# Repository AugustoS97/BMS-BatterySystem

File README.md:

# BMS-BatterySystem
Repositorio con el diseño de un BMS y una batería como Trabajo de Fin de Máster.
- Autor: Augusto Samuel Hernández Martín
- Tutor: Fernando Luis Rosa González
- Co-Tutor: Iván Rodríguez Méndez
- Titulación: Máster en Ingeniería Industrial
- Universidad de La Laguna, 2021

# Licencia
- El paquete: [GPLv3](LICENSE) © 2021 Augusto Samuel Hernández Martín - Universidad de La Laguna

# Resumen 
El presente Trabajo Fin de Máster consiste en el diseñado y fabricación de un Sistema de Gestión de Batería (BMS), así como una batería modular configurable a diferentes tensiones y capacidades, con el objetivo de poder alimentar sistemas electrónicos aislados como los dispositivos de capturas de índices de significación eco-acústicos. Se ha llevado a cabo el diseño electrónico de los diferentes módulos que forman el sistema de alimentación y gestión así como el cálculo y diseño de la batería a partir de celdas de ion-litio y su estructura mecánica. Para poder alimentar dicho sistema se ha dimensionado una posible instalación generadora, empleando energía fotovoltaica. Finalmente, se ha realizado la fabricación de los distintos elementos, tanto mecánicos como electrónicos, y el desarrollo software de las diferentes herramientas necesarias para la configuración del BMS, la captura y el análisis de los datos generados. Por último, se han propuesto y analizado diferentes aplicaciones, además de la mencionada como objetivo principal del proyecto, para este sistema de BMS y acumulador.

# Abstract

In the present Master’s Degree Final Project, a Battery Management System (BMS) has been designed and manufactured, as well as a modular battery configurable at different voltages and capacities, with the aim of being able to power isolated electronic systems such as devices for capturing eco-acoustic significance indexes. The electronic design of the different modules that make up the power supply and management system has been carried out, as well as the calculation and design of the battery based on lithium-ion cells and its mechanical structure. In order to be able to supply this system, a possible generating installation has been dimensioned, using photovoltaic energy. Finally, the manufacture of the different elements, both mechanical and electronic, and the software development of the different tools necessary for the configuration of the BMS and the capture and analysis of the data generated have been carried out. Finally, different applications have been proposed and analysed, in addition to the one mentioned as the main objective of the project, for this BMS and accumulator system.

# Imágenes del sistema desarrollado

# Sistema diseñado

El diagrama de bloques del sistema de alimentación y la batería es el siguiente:

La batería diseñada es la siguiente:

Los módulos electrónicos diseñados son los siguientes:

## BMS

## CAN2Serial

## CAN2RS485

# Contenido del repositorio

## Software
- BMS CAN Programmer: Puede encontrarse la herramienta BMS_CAN_Programer_GUI que debe ejecutarse en Linux con Qt 5 instalado. Y el firmware preparado para grabar en un ATMega 328P empleando la herramienta PlatformIo que realiza la conversión de los mensajes CAN del BMS desarrollado a mensajes serial que son leídos por la herramienta BMS_CAN_Programmer_GUI.
- SOC_estimation: Contiene los ficheros .csv de diferentes ensayos realizados a las celdas INR21700 de Samsung y en el directorio /src el script a ejecutar por terminal para obtener las curvas del ensayo. La carpeta /figures contiene las gráficas generadas.
- SmartBMS: Contiene el firmware del microcontrolador ATMega 328P del módulo de BMS. Debe flashearse empleando Platformio.
- bms_data_processing: Herramienta para ejecutar desde terminal e indicar la ruta del fichero .csv de datos del BMS generado así como número de celdas en serie y número de termistores.
-  power-monitor: Herramienta para instalar en una Raspberry Pi 3B+ que monitoriza el consumo de la misma a partir de las lecturas del integrado INA219 vía I2C. Almacena los ficheros capturados en un .json dentro del directorio /usr/share/power/data. Se generta un serivicio del sistema que puede ser gestionado mediante systemd.
-  power-data-processing: Herramienta que genera los gráficos de los datos capturados por power-monitor. Accede directamente a la ruta /home/$USER/power-data/data. Los diferentes ficheros python deben ubicarse en /home/$USER/power-data/src.

## Diseno-Electronico
- SmartBMS: Módulo electrónico de un BMS pra la medición de hasta 12 paquetes de celdas en serie, con comunicación CAN y medición de hasta 32 termistores NTC de 10KOhm. Opera con tensiones de alimentación de hasta 75V.
- CAN2Serial: Módulo electrónico para la interfaz de conversión de CAN a Serial para emplear la herramienta BMS_Programer_GUI y configurar el BMS.
- EPSolar-CAN: Módulo electrónico para la conversión de los mensajes CAN del BMS a mensajes para un cargador solar EPEver (mediante RS485).

## Diseno-Mecanico
- Bateria_horizontal.FCStd: Fichero FreeCAD con el diseño de un sistema de batería modular de 14.4V y 84Ah.
- Carcasa_Can2Serial.FCStd: Fichero FreeCAD con el diseno e la carcasa para la placa de circuito impreso de CAN2Serial
- STL: Contiene los modelos 3D de las diferentes piezas.

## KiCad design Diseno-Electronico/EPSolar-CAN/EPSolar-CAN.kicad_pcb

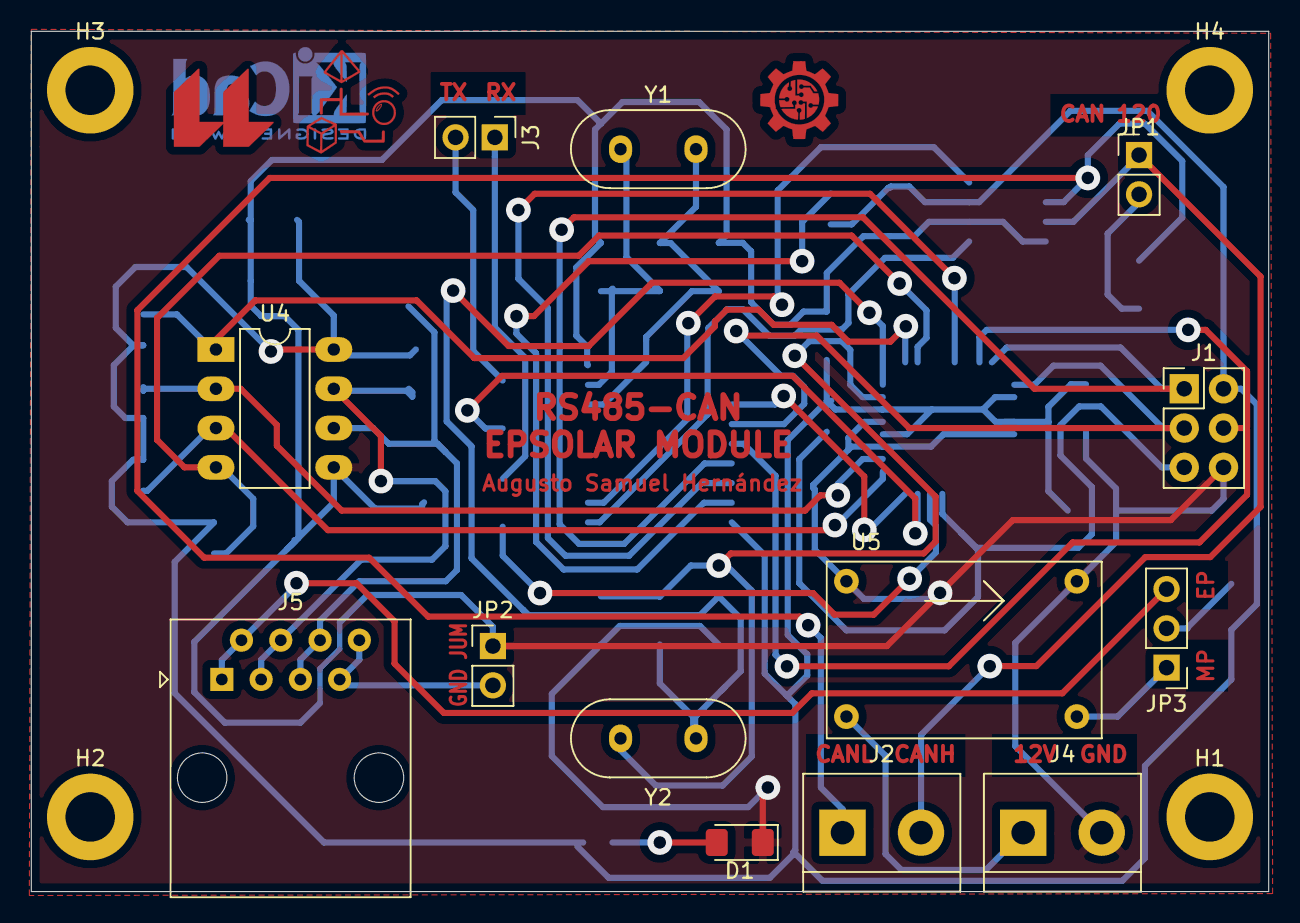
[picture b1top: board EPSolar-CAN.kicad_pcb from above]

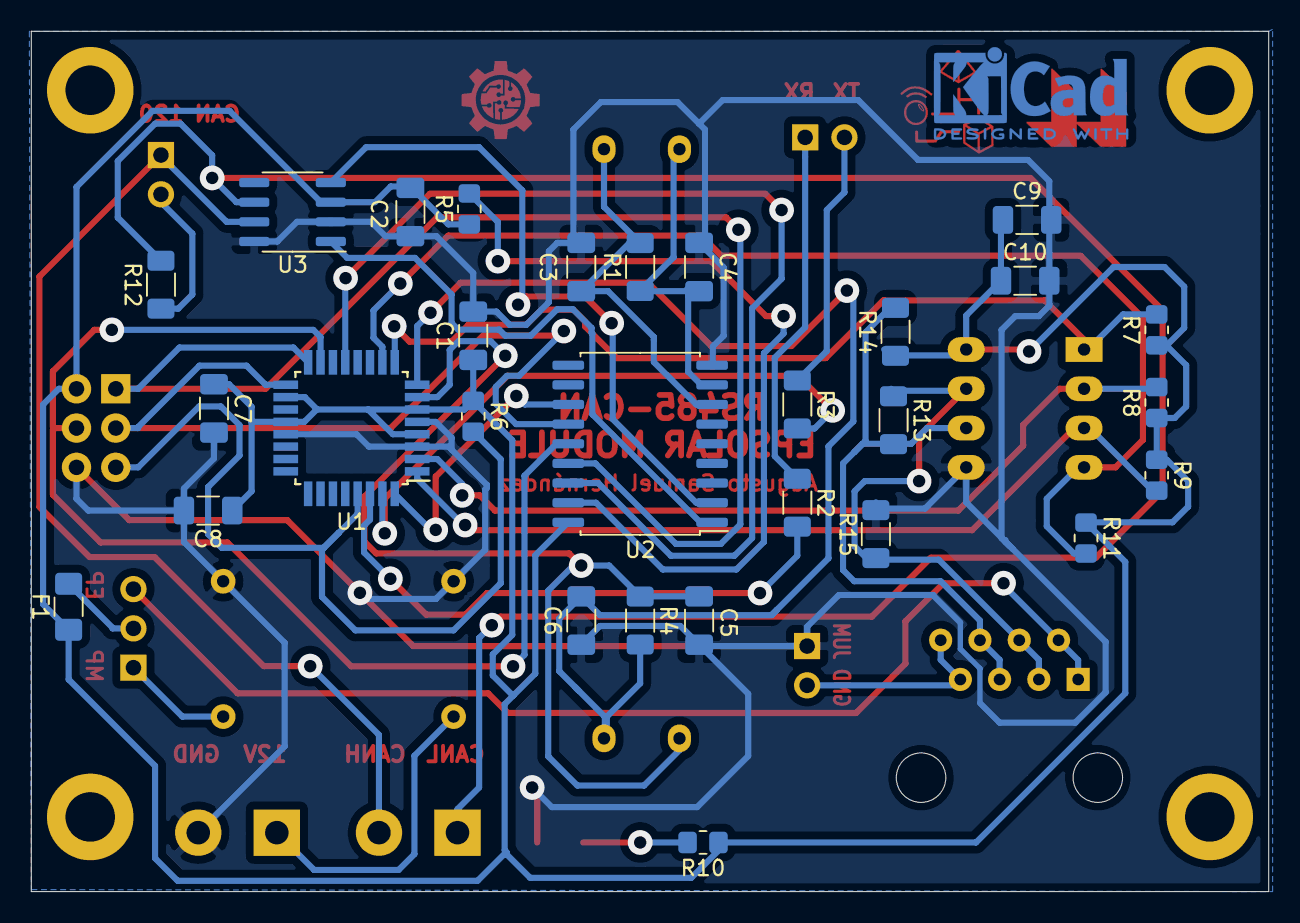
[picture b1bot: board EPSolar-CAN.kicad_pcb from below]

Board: 2 copper layers, 80.0 x 55.6 mm, 46 parts (29 on the bottom side), 34 nets.

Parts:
C1, C2: 100n; C_1206_3216Metric_Pad1.33x1.80mm_HandSolder
C3, C4, C5, C6: 22pF; C_1206_3216Metric_Pad1.33x1.80mm_HandSolder
C7: 100nF; C_1206_3216Metric_Pad1.33x1.80mm_HandSolder
C8: 1uF; C_1206_3216Metric_Pad1.33x1.80mm_HandSolder
C9: 10uF; C_1206_3216Metric_Pad1.33x1.80mm_HandSolder
C10: 0.1uF; C_1206_3216Metric_Pad1.33x1.80mm_HandSolder
D1: LED; LED_1206_3216Metric_Pad1.42x1.75mm_HandSolder
F1: Fuse; Fuse_1206_3216Metric_Pad1.42x1.75mm_HandSolder
H1, H2, H3, H4: MountingHole_Pad-Mechanical; MountingHole_3.2mm_M3_DIN965_Pad
J1: Conn_ICSP; PinHeader_2x03_P2.54mm_Vertical
J2: CAN_conn; TerminalBlock_bornier-2_P5.08mm
J3: Serial_TTL_Conn; PinHeader_1x02_P2.54mm_Vertical
J4: Power_Conn; TerminalBlock_bornier-2_P5.08mm
J5: RJ45; RJ45_Amphenol_54602-x08_Horizontal
JP1: EndBus_R_Jumper; PinHeader_1x02_P2.54mm_Vertical
JP2: Jumper_GND_RS485; PinHeader_1x02_P2.54mm_Vertical
JP3: Jumper_3_Open; PinHeader_1x03_P2.54mm_Vertical
R1, R4: 1M; R_1206_3216Metric_Pad1.30x1.75mm_HandSolder
R2, R3: 220R; R_1206_3216Metric_Pad1.30x1.75mm_HandSolder
R5, R6, R7, R8, R9, R11: 10k; R_0805_2012Metric_Pad1.20x1.40mm_HandSolder
R10: 1k; R_0805_2012Metric_Pad1.20x1.40mm_HandSolder
R12, R13: 120R; R_1206_3216Metric_Pad1.30x1.75mm_HandSolder
R14, R15: 20k; R_1206_3216Metric_Pad1.30x1.75mm_HandSolder
U1: ATmega328P-PU-TQFP-Arduino; TQFP-32_7x7mm_P0.8mm
U2: MCP2515-xSO; SOIC-18W_7.5x11.6mm_P1.27mm
U3: TJA1050T-SmartBMS; SOIC-8_3.9x4.9mm_P1.27mm
U4: MAX485E; DIP-8_W7.62mm_LongPads
U5: MP2307
Y1: 8MHz; Crystal_HC49-U_Vertical
Y2: 16MHz; Crystal_HC49-U_Vertical

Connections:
5V-EPSOLAR: J5.1, J5.2, JP3.3
5V-MP2307: JP3.1, U5.3
5V-PreFuse: F1.2, JP3.2
+5V: C1.1, C2.1, C7.1, C8.1, C9.1, C10.1, F1.1, J1.2, R5.1, R6.1, R7.1, R8.1, R9.1, R10.1, R11.1, R14.1, U1.4, U1.6, U1.18, U1.20, U2.18, U3.3, U4.8
+12V: J4.1, U5.1
/MISO: J1.1, U1.16, U2.15
/MOSI: J1.4, U1.15, U2.14
/RESET: J1.5, R6.2, U1.29
/SCK: J1.3, U1.17, U2.13
/SS_MCP: U1.13, U2.16
A: J5.5, J5.6, R13.2, R14.2, U4.6
B: J5.3, J5.4, R13.1, R15.1, U4.7
CANH: J2.2, JP1.1, U3.7
CANL: J2.1, R12.2, U3.6
DE-485: R9.2, U1.1, U4.3
DI-485: R11.2, U1.10, U4.4
GND: C1.2, C2.2, C3.1, C4.1, C5.1, C6.1, C7.2, C8.2, C9.2, C10.2, D1.1, J1.6, J4.2, JP2.1, R15.2, U1.3, U1.5, U1.21, U2.9, U3.2, U3.8, U4.5, U5.2, U5.4
GND-EPSOLAR: J5.7, J5.8, JP2.2
MCP_INT: U1.32, U2.12
unnamed: C3.2, R1.2, U2.7, Y1.2
unnamed: C4.2, R1.1, U2.8, Y1.1
unnamed: C5.2, R4.1, U1.7, Y2.1
unnamed: C6.2, R4.2, U1.8, Y2.2
unnamed: D1.2, R10.2
unnamed: JP1.2, R12.1
unnamed: R2.2, U1.30
unnamed: R3.2, U1.31
unnamed: R5.2, U2.17
RE-485: R8.2, U1.2, U4.2
RO-485: R7.2, U1.9, U4.1
RXCAN: U2.2, U3.4
RX_TTL: J3.1, R2.1
TXCAN: U2.1, U3.1
TX_TTL: J3.2, R3.1

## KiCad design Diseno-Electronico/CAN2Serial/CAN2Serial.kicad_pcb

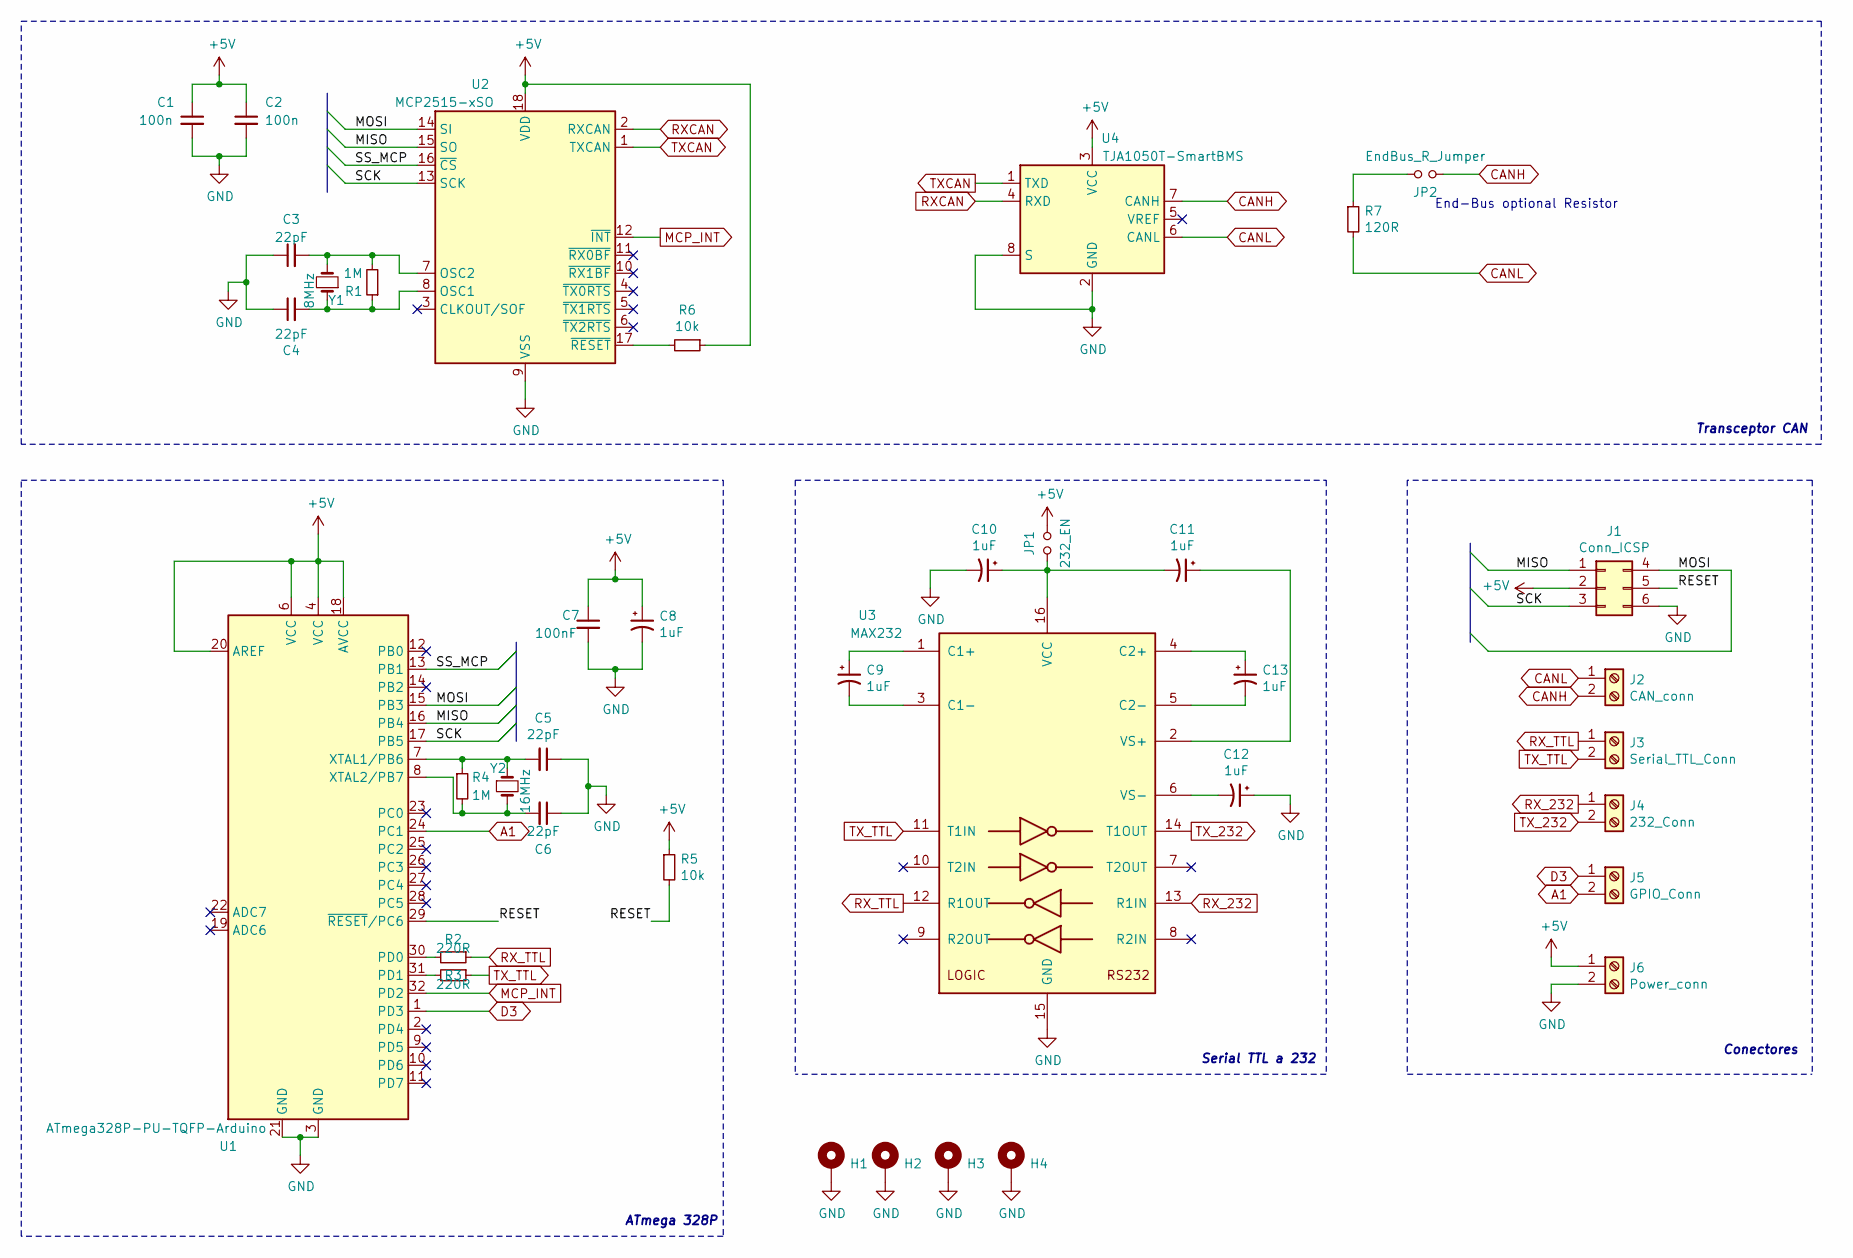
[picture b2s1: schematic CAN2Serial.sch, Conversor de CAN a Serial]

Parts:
C1, C2: 100n; C_1206_3216Metric_Pad1.33x1.80mm_HandSolder
C3, C4, C5, C6: 22pF; C_1206_3216Metric_Pad1.33x1.80mm_HandSolder
C7: 100nF; C_1206_3216Metric_Pad1.33x1.80mm_HandSolder
C8, C9, C10, C11, C12, C13: 1uF; CP_Radial_D4.0mm_P1.50mm
H1, H2, H3, H4: MountingHole_Pad-Mechanical; MountingHole_3.2mm_M3_DIN965_Pad
J1: Conn_ICSP; PinHeader_2x03_P2.54mm_Vertical
J2: CAN_conn; TerminalBlock_bornier-2_P5.08mm
J3: Serial_TTL_Conn; TerminalBlock_bornier-2_P5.08mm
J4: 232_Conn; TerminalBlock_bornier-2_P5.08mm
J5: GPIO_Conn; PinHeader_1x02_P2.54mm_Vertical
J6: Power_conn; TerminalBlock_bornier-2_P5.08mm
JP1: 232_EN; SolderJumper-2_P1.3mm_Open_RoundedPad1.0x1.5mm
JP2: EndBus_R_Jumper; SolderJumper-2_P1.3mm_Open_RoundedPad1.0x1.5mm
R1, R4: 1M; R_1206_3216Metric_Pad1.30x1.75mm_HandSolder
R2, R3: 220R; R_1206_3216Metric_Pad1.30x1.75mm_HandSolder
R5, R6: 10k; R_0805_2012Metric_Pad1.20x1.40mm_HandSolder
R7: 120R; R_0805_2012Metric_Pad1.20x1.40mm_HandSolder
U1: ATmega328P-PU-TQFP-Arduino; TQFP-32_7x7mm_P0.8mm
U2: MCP2515-xSO; SOIC-18W_7.5x11.6mm_P1.27mm
U3: MAX232; DIP-16_W7.62mm_Socket
U4: TJA1050T-SmartBMS; SOIC-8_3.9x4.9mm_P1.27mm
Y1: 8MHz; Crystal_HC49-U_Vertical
Y2: 16MHz; Crystal_HC49-U_Vertical

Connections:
+5V: C1.1, C2.1, C7.1, C8.1, J1.2, J6.1, JP1.2, R5.1, R6.1, U1.4 (VCC), U1.6 (VCC), U1.18 (AVCC), U1.20 (AREF), U2.18 (VDD), U4.3 (VCC); also elsewhere on the board
/MISO: J1.1, U1.16 (PB4), U2.15 (SO)
/MOSI: J1.4, U1.15 (PB3), U2.14 (SI)
/RESET: J1.5, R5.2, U1.29 (~RESET~/PC6)
/SCK: J1.3, U1.17 (PB5), U2.13 (SCK)
/SS_MCP: U1.13 (PB1), U2.16 (~CS)
A1: J5.2, U1.24 (PC1)
CANH: J2.2, JP2.1, U4.7 (CANH); also elsewhere on the board
CANL: J2.1, R7.2, U4.6 (CANL); also elsewhere on the board
D3: J5.1, U1.1 (PD3)
GND: C1.2, C2.2, C3.1, C4.1, C5.1, C6.1, C7.2, C8.2, C10.2, C12.1, H1.1, H2.1, H3.1, H4.1, J1.6, J6.2, U1.3 (GND), U1.5 (GND), U1.21 (GND), U2.9 (VSS), U3.15 (GND), U4.2 (GND), U4.8 (S); also elsewhere on the board
MCP_INT: U1.32 (PD2), U2.12 (~INT)
unnamed: C3.2, R1.2, U2.7 (OSC2), Y1.2
unnamed: C4.2, R1.1, U2.8 (OSC1), Y1.1
unnamed: C5.2, R4.1, U1.7 (XTAL1/PB6), Y2.1
unnamed: C6.2, R4.2, U1.8 (XTAL2/PB7), Y2.2
unnamed: C9.1, U3.1 (C1+)
unnamed: C9.2, U3.3 (C1-)
unnamed: C10.1, C11.2, JP1.1, U3.16 (VCC)
unnamed: C11.1, U3.2 (VS+)
unnamed: C12.2, U3.6 (VS-)
unnamed: C13.1, U3.4 (C2+)
unnamed: C13.2, U3.5 (C2-)
unnamed: JP2.2, R7.1
unnamed: R2.2, U1.30 (PD0)
unnamed: R3.2, U1.31 (PD1)
unnamed: R6.2, U2.17 (~RESET)
RXCAN: U2.2 (RXCAN), U4.4 (RXD); also elsewhere on the board
RX_232: J4.1, U3.13 (R1IN)
RX_TTL: J3.1, R2.1, U3.12 (R1OUT)
TXCAN: U2.1 (TXCAN), U4.1 (TXD); also elsewhere on the board
TX_232: J4.2, U3.14 (T1OUT)
TX_TTL: J3.2, R3.1, U3.11 (T1IN)

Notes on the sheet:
End-Bus optional Resistor
Transceptor CAN
Conectores
Serial TTL a 232
ATmega 328P

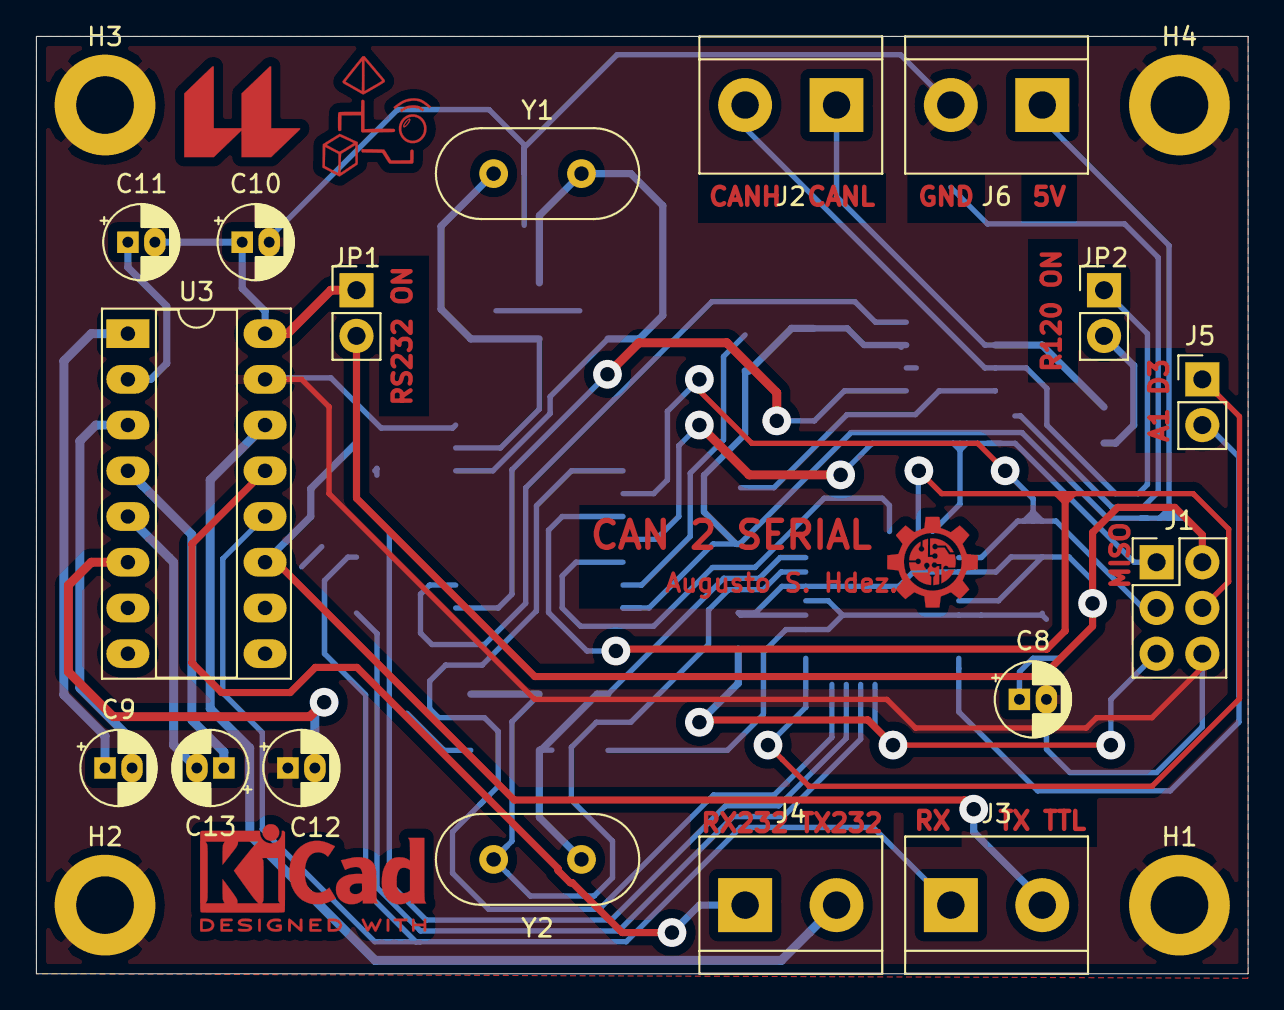
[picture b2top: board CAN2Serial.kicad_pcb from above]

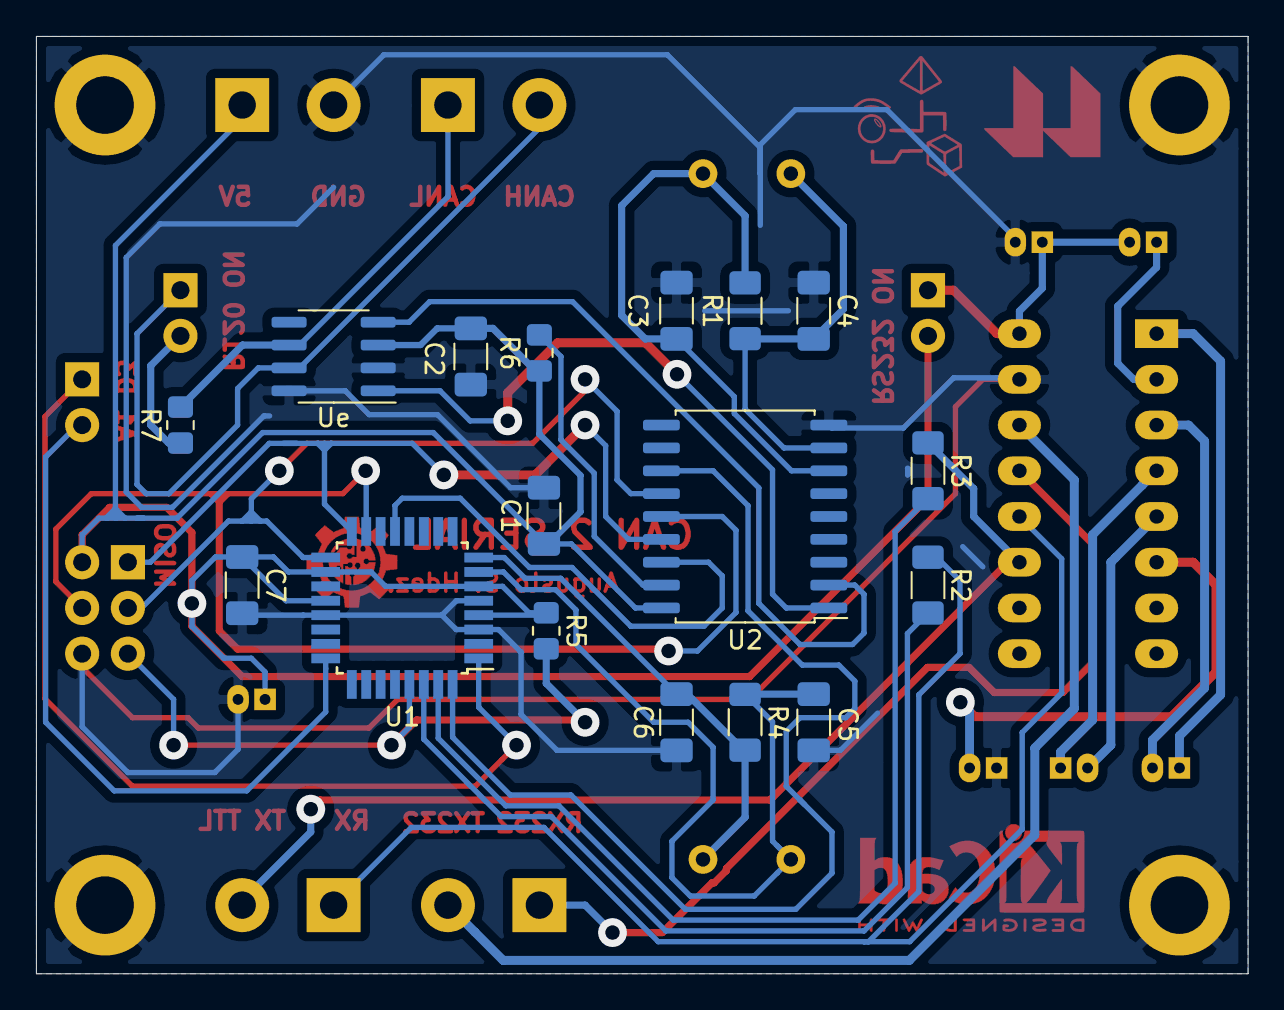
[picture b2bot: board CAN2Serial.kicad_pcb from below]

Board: 2 copper layers, 67.3 x 52.1 mm, 38 parts (17 on the bottom side), 33 nets.

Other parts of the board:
Ue: TJA1050T-SmartBMS; SOIC-8_3.9x4.9mm_P1.27mm

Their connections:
+5V: Ue.3; also elsewhere on the board
CANH: Ue.7; also elsewhere on the board
CANL: Ue.6; also elsewhere on the board
GND: Ue.2, Ue.8; also elsewhere on the board
RXCAN: Ue.4; also elsewhere on the board
TXCAN: Ue.1; also elsewhere on the board

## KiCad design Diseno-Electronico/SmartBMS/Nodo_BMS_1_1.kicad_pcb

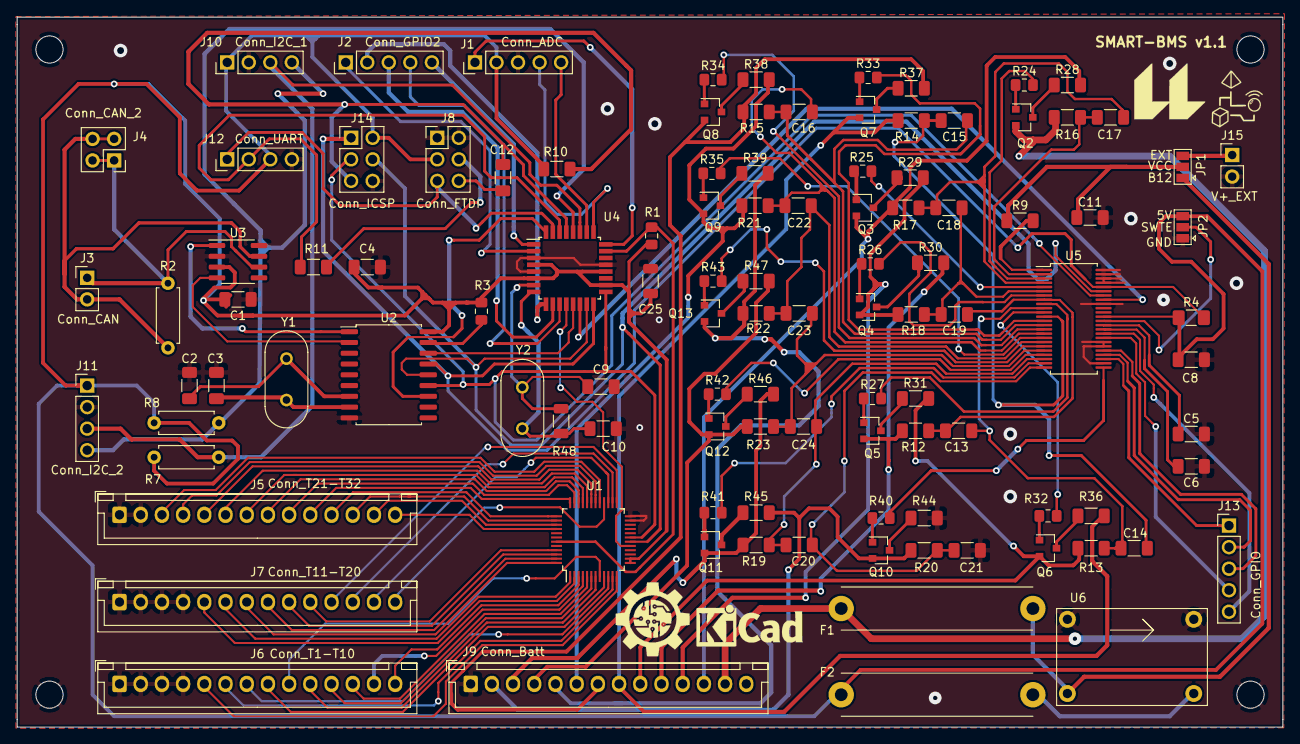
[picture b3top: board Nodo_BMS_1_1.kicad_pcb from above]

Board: 2 copper layers, 149.2 x 83.7 mm, 113 parts (0 on the bottom side), 139 nets.

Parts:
C1, C4, C11: 100n; R_1206_3216Metric_Pad1.30x1.75mm_HandSolder
C2, C3: 27pF; R_1206_3216Metric_Pad1.30x1.75mm_HandSolder
C5, C6, C8: 1u; R_1206_3216Metric_Pad1.30x1.75mm_HandSolder
C9: 12-22 pF; R_1206_3216Metric_Pad1.30x1.75mm_HandSolder
C10: 12-22pF; R_1206_3216Metric_Pad1.30x1.75mm_HandSolder
C12: 100nF; R_1206_3216Metric_Pad1.30x1.75mm_HandSolder
C13, C14, C15, C16, C17, C18, C19, C20, C21, C22, C23, C24: 10n; R_1206_3216Metric_Pad1.30x1.75mm_HandSolder
C25: 100nF; R_1206_3216Metric
F1: fuse 1A; Fuseholder_Cylinder-5x20mm_Stelvio-Kontek_PTF78_Horizontal_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
F2: fuse 0,5 A; Fuseholder_Cylinder-5x20mm_Stelvio-Kontek_PTF78_Horizontal_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
H1, H2, H3, H4: MountingHole; MountingHole_3.2mm_M3
J1: Conn_ADC; PinHeader_1x05_P2.54mm_Vertical
J2: Conn_GPIO2; PinHeader_1x05_P2.54mm_Vertical
J3: Conn_CAN; PinHeader_1x02_P2.54mm_Vertical
J4: Conn_CAN_2; PinSocket_2x02_P2.54mm_Vertical
J5: Conn_T21-T32; JST_XH_B14B-XH-A_1x14_P2.50mm_Vertical
J6: Conn_T1-T10; JST_XH_B14B-XH-A_1x14_P2.50mm_Vertical
J7: Conn_T11-T20; JST_XH_B14B-XH-A_1x14_P2.50mm_Vertical
J8: Conn_FTDI; PinHeader_2x03_P2.54mm_Vertical
J9: Conn_Batt; JST_XH_B14B-XH-A_1x14_P2.50mm_Vertical
J10: Conn_I2C_1; PinHeader_1x04_P2.54mm_Vertical
J11: Conn_I2C_2; PinHeader_1x04_P2.54mm_Vertical
J12: Conn_UART; PinHeader_1x04_P2.54mm_Vertical
J13: Conn_GPIO; PinHeader_1x05_P2.54mm_Vertical
J14: Conn_ICSP; PinHeader_2x03_P2.54mm_Vertical
J15: V+_EXT; PinHeader_1x02_P2.54mm_Vertical
JP1, JP2: Jumper_3_Open; SolderJumper-3_P1.3mm_Open_Pad1.0x1.5mm
Q2, Q3, Q4, Q5, Q6, Q7, Q8, Q9, Q10, Q11, Q12, Q13: BSS308PE; SOT-23
R1: 10K; R_0805_2012Metric_Pad1.15x1.40mm_HandSolder
R2, R7, R8: 120R; R_Axial_DIN0207_L6.3mm_D2.5mm_P7.62mm_Horizontal
R3: 10k; R_0805_2012Metric_Pad1.15x1.40mm_HandSolder
R4: 5k; R_1206_3216Metric_Pad1.42x1.75mm_HandSolder
R9, R12, R13, R14, R15, R16, R17, R18, R19, R20, R21, R22, R23: 100R; R_1206_3216Metric_Pad1.30x1.75mm_HandSolder
R10: 10k; R_1206_3216Metric_Pad1.30x1.75mm_HandSolder
R11: 1k; R_1206_3216Metric_Pad1.30x1.75mm_HandSolder
R24, R25, R26, R27, R32, R33, R34, R35, R40, R41, R42, R43: 1k; R_0805_2012Metric_Pad1.15x1.40mm_HandSolder
R28, R29, R30, R31, R36, R37, R38, R39, R44, R45, R46, R47: 10R, 2W; R_1206_3216Metric_Pad1.30x1.75mm_HandSolder
R48: 1M; R_1206_3216Metric
U1: ADG731; TQFP-48_7x7mm_P0.5mm
U2: MCP2515-xSO; SOIC-18W_7.5x11.6mm_P1.27mm
U3: TJA1050T; SOIC-8_3.9x4.9mm_P1.27mm
U4: ATmega328P-PU; TQFP-32_7x7mm_P0.8mm
U5: LTC6804-2; SSOP-48_5.3x12.8mm_P0.5mm
U6: MP2307
Y1: 8MHz; Crystal_HC49-4H_Vertical
Y2: 16MHz; Crystal_HC49-4H_Vertical

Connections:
+5V: C1.1, C4.1, C8.1, C25.1, F2.1, J1.2, J8.3, J10.1, J11.1, J12.3, J14.2, JP2.3, R1.2, R3.1, R4.1, R7.1, R8.1, R10.1, U1.13, U1.14, U2.18, U3.3, U4.4, U4.6, U4.18, U4.20, U5.37
/B1: J9.2, Q10.2, R20.1, R45.2
/B2: J9.3, Q11.2, R19.1, R46.2
/B3: J9.4, Q12.2, R23.1, R47.2
/B4: J9.5, Q13.2, R22.1, R39.2
/B5: J9.6, Q9.2, R21.1, R38.2
/B6: J9.7, Q8.2, R15.1, R37.2
/B7: J9.8, Q7.2, R14.1, R36.2
/B8: J9.9, Q6.2, R13.1, R31.2
/B9: J9.10, Q5.2, R12.1, R30.2
/B10: J9.11, Q4.2, R18.1, R29.2
/B11: J9.12, Q3.2, R17.1, R28.2
/B12: F1.1, J9.13, Q2.2, R16.1
/C1: C20.2, C21.1, R20.2, U5.24
/C2: C20.1, C24.2, R19.2, U5.22
/C3: C23.2, C24.1, R23.2, U5.20
/C4: C22.2, C23.1, R22.2, U5.18
/C5: C16.2, C22.1, R21.2, U5.16
/C6: C15.2, C16.1, R15.2, U5.14
/C7: C14.2, C15.1, R14.2, U5.12
/C8: C13.2, C14.1, R13.2, U5.10
/C9: C13.1, C19.2, R12.2, U5.8
/C10: C18.2, C19.1, R18.2, U5.6
/C11: C17.2, C18.1, R17.2, U5.4
/C12: C17.1, R16.2, U5.2
/MISO: J14.1, R4.2, U2.15, U4.16, U5.44
/MOSI: J14.4, U1.18, U2.14, U4.15, U5.43
/RESET: C12.2, J14.5, R10.2, U4.29
/RTS: C12.1, J8.6
/S1: R40.2, U5.25
/S2: R41.2, U5.23
/S3: R42.2, U5.21
/S4: R43.2, U5.19
/S5: R35.2, U5.17
/S6: R34.2, U5.15
/S7: R33.2, U5.13
/S8: R32.2, U5.11
/S9: R27.2, U5.9
/S10: R26.2, U5.7
/S11: R25.2, U5.5
/S12: R24.2, U5.3
/SCK: J14.3, U1.19, U2.13, U4.17, U5.42
/SCL: J10.4, J11.4, R8.2, U4.28
/SDA: J10.3, J11.3, R7.2, U4.27
/SS_LTC: U4.14, U5.41
/SS_MCP: U2.16, U4.13
/SWTEN: JP2.2, U5.36
/SYNC_MUX: U1.17, U4.12
/TXD: J8.4, R11.1
/V+_EXT: J15.1, JP1.3
/VREF1: C5.1, U5.35
/VREF2: C6.1, U5.34
A1: J1.1, U4.24
A2: J1.4, U4.25
A3: J1.5, U4.26
CANH: J3.2, J4.2, J4.4, R2.1, U3.7
CANL: J3.1, J4.1, J4.3, R2.2, U3.6
D4: J2.1, U4.2
D5: J2.2, U4.9
D6: J2.3, U4.10
D7: J2.4, U4.11
GND: C1.2, C2.2, C3.2, C4.2, C5.2, C6.2, C8.2, C9.2, C10.2, C11.2, C21.2, C25.2, H1.1, H2.1, H3.1, H4.1, J1.3, J5.1, J5.2, J6.1, J6.2, J6.3, J6.4, J7.1, J7.2, J7.3, J7.4, J8.1, J8.2, J9.1, J10.2, J11.2, J12.4, J14.6, J15.2, JP2.1, R44.2, U1.23, U1.24, U2.9, U3.2, U3.8, U4.3, U4.5, U4.21, U5.26, U5.30, U5.31, U5.40, U5.45, U5.46, U5.47, U5.48, U6.2, U6.4
GPIO1: J13.1, U5.27
GPIO2: J13.2, U5.28
GPIO3: J13.3, U5.29
GPIO4: J13.4, U5.32
GPIO5: J13.5, U5.33
INT1: J2.5, U4.1
MCP_INT: U2.12, U4.32
NTC_ADC: R1.1, U1.43, U4.23
unnamed: C2.1, U2.7, Y1.1
unnamed: C3.1, U2.8, Y1.2
unnamed: C9.1, R48.1, U4.7, Y2.2
unnamed: C10.1, R48.2, U4.8, Y2.1
unnamed: F1.2, JP1.1, U6.1
unnamed: F2.2, U6.3
unnamed: Q2.1, R24.1
unnamed: Q2.3, R28.1
unnamed: Q3.1, R25.1
unnamed: Q3.3, R29.1
unnamed: Q4.1, R26.1
unnamed: Q4.3, R30.1
unnamed: Q5.1, R27.1
unnamed: Q5.3, R31.1
unnamed: Q6.1, R32.1
unnamed: Q6.3, R36.1
unnamed: Q7.1, R33.1
unnamed: Q7.3, R37.1
unnamed: Q8.1, R34.1
unnamed: Q8.3, R38.1
unnamed: Q9.1, R35.1
unnamed: Q9.3, R39.1
unnamed: Q10.1, R40.1
unnamed: Q10.3, R44.1
unnamed: Q11.1, R41.1
unnamed: Q11.3, R45.1
unnamed: Q12.1, R42.1
unnamed: Q12.3, R46.1
unnamed: Q13.1, R43.1
unnamed: Q13.3, R47.1
unnamed: R3.2, U2.17
unnamed: R9.2, U5.1
RX: J12.2, R11.2, U4.30
RXCAN: U2.2, U3.4
T1: J6.5, U1.12
T2: J6.6, U1.11
T3: J6.7, U1.10
T4: J6.8, U1.9
T5: J6.9, U1.8
T6: J6.10, U1.7
T7: J6.11, U1.6
T8: J6.12, U1.5
T9: J6.13, U1.4
T10: J6.14, U1.3
T11: J7.5, U1.2
T12: J7.6, U1.1
T13: J7.7, U1.48
T14: J7.8, U1.47
T15: J7.9, U1.46
T16: J7.10, U1.45
T17: J7.11, U1.25
T18: J7.12, U1.26
T19: J7.13, U1.27
T20: J7.14, U1.28
T21: J5.3, U1.29
T22: J5.4, U1.30
T23: J5.5, U1.31
T24: J5.6, U1.32
T25: J5.7, U1.33
T26: J5.8, U1.34
T27: J5.9, U1.35
T28: J5.10, U1.36
T29: J5.11, U1.37
T30: J5.12, U1.38
T31: J5.13, U1.39
T32: J5.14, U1.40
TX: J8.5, J12.1, U4.31
TXCAN: U2.1, U3.1
VCC: C11.1, JP1.2, R9.1

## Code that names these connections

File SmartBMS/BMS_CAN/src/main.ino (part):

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
  |  aux_codes[0][0]| aux_codes[0][1] |  aux_codes[0][2]|  aux_codes[0][3]|  aux_codes[0][4]|  aux_codes[0][5]| aux_codes[1][0] |aux_codes[1][1]|  .....    |
  |-----------------|-----------------|-----------------|-----------------|-----------------|-----------------|-----------------|---------------|-----------|
  |IC1 GPIO1        |IC1 GPIO2        |IC1 GPIO3        |IC1 GPIO4        |IC1 GPIO5        |IC1 Vref2        |IC2 GPIO1        |IC2 GPIO2      |  .....    |
*/


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  }

  //Se miden todas las temperaturas de las celdas y se guardan en cell_temp. Además se obtiene la T_max
  T_max = measure_all_temp(cell_temp, N_NTC, BETTA, To, Ro, Raux, Vcc, PIN_ANALOG_NTC, PIN_SYNC_MUX);

  //Se conviertes las temperaturas a mensajes CAN
  temp_to_can_msg(cell_temp, N_NTC, canTempMsg1, canTempMsg2, canTempMsg3, canTempMsg4);
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
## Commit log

2021-08-26 Añadidos todos los codigos y las graficas generadas.
2021-09-05 Rename LICENSE to LICENSE.md
2021-09-05 Create LICENSE
2021-09-20 añadidos graficos para el readme
2021-09-20 Añadida imagen en readme
2021-09-20 Reestructurado el repo.
2021-09-20 Add license to different READMEs
2021-09-21 Some img add.
2021-09-21 Añado la memoria del TFM
